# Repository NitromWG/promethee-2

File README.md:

# Prométhée

Logiciel libre d'ingénierie intégrée : CAO mécanique, mise en plan, CAO électronique et électrique dans un seul modèle. Le cahier des charges complet décrit le produit visé ; ce dépôt en est l'implémentation, construite étape par étape.

Le principe fondateur, déjà démontré : **la carte électronique et son boîtier forment un seul modèle**. Les piliers suivent les trous de fixation, les découpes de paroi suivent les connecteurs, les perçages du couvercle suivent les LED et les boutons, la hauteur du boîtier suit le composant le plus haut, et les vérifications tournent à chaque modification.

## État

Phase 0 (cadrage), voir [ETAT.md](ETAT.md) et [FEUILLE_DE_ROUTE.md](FEUILLE_DE_ROUTE.md).

| Partie | Contenu |
| --- | --- |
| `noyau/` | Modèle unique carte + boîtier, grandeurs dérivées, vérifications et corrections ; conception électronique (schéma, connectivité, ERC, circuit imprimé, zones, DRC, routage, fabrication, publication) (C++20) |
| `geometrie/` | Pièces exactes en B-rep OpenCascade, export STEP (noms, couleurs) et STL |
| `app/` | Application de bureau Qt 6 : vue Carte, vue Boîtier 3D OpenCascade, panneau, vérifications, nomenclature |
| `outils/` | `promethee`, l'outil en ligne de commande (mode sans écran) |
| `en-ligne/` | `promethee-en-ligne`, le seul programme qui ouvre le réseau (PLM, distributeurs, ERP, tickets), fonction par fonction et seulement si l'utilisateur l'active ; il lit et remplit les fichiers du dossier d'équipe, Prométhée ne voit que ces fichiers |
| `tests/` | Tests unitaires, géométriques, et comparaison cas par cas avec le prototype |
| `prototype-web/` | Prototype du jalon 0, implémentation de référence en JavaScript |
| `docs/adr/` | Décisions d'architecture |

## Essayer l'application sous Windows

Ouvrir l'onglet Actions du dépôt, cliquer sur la dernière compilation au vert, télécharger le paquet `Promethee-Windows`, le décompresser et lancer `Promethee.exe`. Aucune installation n'est nécessaire. Le paquet contient son LISEZMOI (lancement, journal, récupération, limites connues), la source correspondante, les licences, un inventaire SPDX et la somme SHA-256 de chaque fichier.

Apparence : Affichage › Thème, ou le choix « Apparence » de l'accueil. Prométhée (recommandé, par défaut) garde une interface bleu nuit autour de documents sur papier clair ; Clair, Sombre et Contraste élevé suivent ; Selon le système reprend le réglage clair ou sombre de Windows. Le changement est immédiat et gardé d'une session à l'autre ; l'impression et les PDF restent clairs.

Vue Carte : glisser un composant, un trou, ou une poignée du bord de la carte après avoir cliqué dessus ; molette pour zoomer ; double-clic pour pivoter un composant. Vue Boîtier : bouton gauche pour tourner autour, bouton droit pour déplacer, molette pour zoomer, cube de vue pour les vues normalisées (touches 0, 1, 3 et 7), boîtier transparent (T). La vue Carte montre la face avant ou la face arrière (B). Le boîtier se montre visible, transparent ou masqué ; le clic droit dans la 3D masque, rend transparent ou supprime un élément. Fichier propose l'import et l'export KiCad (.kicad_pcb), en mettant à jour la carte d'origine.

L'atelier électronique (Ctrl+3) conçoit une carte de bout en bout, sans autre logiciel : schéma (bibliothèque avec aperçu, fils en équerre, étiquettes, alimentations, annotation, vérification électrique en direct, dessin PDF), composants créés à partir de leur liste de broches, valeurs comprises (« 4k7 » = 4,7 kΩ) ou calculées (« 2*R1 »), circuit imprimé tenu à jour à chaque modification du schéma, les écarts risqués attendant au panneau des écarts (F8 synchronise tout), empreinte changée remplacée en place, composant remplacé par un autre article sans perdre ses fils, schéma et circuit côte à côte, placement à la souris, routage à 45° avec vérification d'isolement en direct (X piste, V via, / angle) ou automatique pour les liaisons simples, zones de cuivre, DRC, vue 3D, puis l'onglet Fabrication : santé de la conception, dossier Gerber X2 et Excellon, placement, nomenclature, publication R001… qui verrouille la révision. Ce qui ne se fabrique pas juste ne se publie pas, dérogation ou non : cuivre coupé par le bord, CMS sur la face sans cuivre d'une simple face, profil de fabricant inconnu, brochage non vérifié après un changement de boîtier. Un exemple complet (clignotant à NE555) s'ouvre depuis l'accueil. Schéma : W fil, L étiquette (Maj+L globale), P alimentation, Q non connecté, J jonction, T texte, A bibliothèque, R et Maj+R tourner, X et Y miroir, Origine tout voir ; circuit : F change de face. F1 donne la liste des raccourcis de l'atelier et de l'outil en cours. La souris suffit : chaque touche a son bouton au ruban (groupe Vue : Tout voir, zoom, inspecteur, raccourcis) ou au bandeau de l'outil (pendant une piste : Via, Dessus, Dessous, Retirer le coude, Retirer le tracé, Coude, Terminer), et un essai fait échouer la construction si une action n'a qu'un raccourci. Pendant un fil ou une piste, une autre commande (une jonction, une via à part, une piste gênante supprimée par le clic droit) suspend le tracé, qui reprend ensuite au dernier coude ; la barre du routeur choisit la paire de couches, la largeur, et le type et l'arrivée de la prochaine via. Le bandeau de sélection donne à la souris les modes Remplacer, Ajouter, Basculer et Retirer (Maj, Ctrl et Ctrl+Maj au clavier) ; un appui long immobile sur des objets superposés en ouvre la liste, comme Alt+clic ; le filtre de sélection de la barre d'état exclut des genres d'objets, et clignote quand il bloque un clic. Fichier › Réglages… (Ctrl+,) règle la souris et le pavé tactile : zoom par cran, sens de la molette, zoom autour du curseur ou du centre, défilement au bord pendant un glisser, deux doigts qui zooment ou font défiler, bouton des gestes. Menu à marques dans le schéma et le circuit : le bouton droit tenu immobile montre huit commandes (← Annuler, → Rétablir, ↑ Zoom sur la sélection, ↓ Tout voir, et en diagonale Tourner, Miroir, Supprimer, Dupliquer) ; avec Ctrl, un tracé rapide dans une direction lance la commande sans attendre. Le ruban est décrit par un fichier qui ne cite que des actions du registre (app/ressources/ruban_electronique.json) ; Réglages › Ruban le modifie en glissant une action dans un groupe, et « Rétablir l'original » le rend. Réglages › Clavier choisit si une touche d'outil l'arme ou agit au curseur. Les suites de deux touches existent (P puis V : poser une via au circuit), la première s'annonçant près du curseur ; Maj+A ouvre au curseur le menu Poser ; une bascule faite au clavier (/ : coude) s'annonce près du curseur. Dans l'atelier, les menus de la fenêtre sont les siens : Ctrl+I importe une carte KiCad vers l'électronique, Ctrl+E écrit le dossier de fabrication de la carte. « Schéma électronique » ouvre un schéma seul, dont le circuit imprimé se crée au premier besoin (bouton Circuit du ruban). Ctrl+3 dans un projet sans carte ouvre l'accueil électronique sans rien créer ; une carte se renomme sur place dans l'arbre, se supprime sans fenêtre (Ctrl+Z la rend), et un projet se rouvre sur le dernier atelier utilisé. Les panneaux de l'atelier (Projet, Bibliothèque, Inspecteur, Messages) flottent, s'ancrent, se groupent en onglets ou se ferment ; le bouton Panneaux de la barre d'état (ou Affichage › Panneaux et dispositions) enregistre leur disposition sous un nom, pour soi, dans le projet ou dans un fichier .json à partager, la rappelle et rend la disposition d'origine. La bibliothèque se trie par catégorie, par pertinence (accents ignorés) ou par ordre alphabétique, montre en colonnes les champs choisis d'un clic droit sur son en-tête, et son aperçu passe du symbole à l'empreinte, à la 3D et à la photo (propriété « photo » du composant). Fichier › Enregistrer pour une version précédente… écrit, pour un collègue qui n'a pas migré, un fichier neuf lisible par une version précédente, de la 0.33 à la 0.28 (« carte.pour-0-33.prom »), après la liste de ce qui s'y perd ; chaque migration du format a son inverse, et les schémas JSON de chaque version sont dans docs (schema_projet.json, schema_conception.json, docs/schemas). En ligne de commande : promethee pour-version <projet> <sortie> [version]. Le schéma se fait à la souris : un article se glisse de la bibliothèque sur la feuille (ou sur le circuit pour un trou de fixation), le survol montre l'objet visé et son infobulle, chaque objet a son menu au clic droit, le repère et la valeur s'éditent sur place, le fil part à l'équerre en évitant les symboles et les fils suivent un symbole déplacé ; la vérification électrique ne crie pas pendant le dessin et F7 la fait complète, son panneau groupant les problèmes par cause. Ctrl+F cherche dans tout le projet, schéma et circuit ; « Choisir les semblables » prend les composants de même valeur sur toutes les feuilles et estompe le reste ; une longueur et un angle se tapent pendant un fil (un chiffre ouvre la saisie). Les réglages se cherchent, s'exportent dans un fichier et se relisent, raccourcis, ruban et thème compris ; les couleurs du canevas se règlent une à une, avec une palette vérifiée pour les daltoniens. La fenêtre « Outils de conception » (ruban, groupe Outils) rassemble variantes et coût, revue automatique, comparaison avec un autre fichier, schéma de système, notes, historique local, mise en service et fiabilité, intégrité, logique, fabrication à l'atelier et exigences ; un projet tenu par un autre poste s'ouvre en consultation, avec le nom de celui qui le tient.

L'atelier électrique (Ctrl+4) mène un projet d'électricien de bout en bout, sans autre logiciel. Schéma sur folios CEI 61082 (139 symboles CEI 60617 avec leur fiche « C'est quoi ? », contacts rattachés à leur bobine, renvois croisés, bornes, numéros de fils, circuits types, vérification qui mène au problème d'un clic, appareils personnels dessinés d'après leurs bornes), armoire implantée à l'échelle avec son bilan thermique, faisceau, Grafcet (NF EN CEI 60848 : édition, vérification, simulation, folio, texte structuré pour l'automate), installation basse tension calculée (UTE C 15-105, note de calcul), photovoltaïque (UTE C 15-712-1), tableau de logement (NF C 15-100), boîte à calculs, rapports (nomenclature chiffrée, borniers, câbles, carnet de câblage, liste de coupe, chiffrage) et dossier complet (folios en PDF et en DXF, CSV, plans de perçage). Le bouton « Apprendre » ouvre des parcours guidés dont chaque étape se valide sur le projet. Un exemple (démarrage d'un moteur) s'ouvre depuis l'accueil, et les projets QElectroTech s'importent.

L'atelier Pièces (Ctrl+2) sert à concevoir une pièce de zéro : esquisses cotées et contraintes, extrusion, enlèvement, révolution, congé, chanfrein et coque, dans un arbre de construction modifiable à tout moment. Dans l'esquisseur : L ligne, R rectangle, C cercle, A arc, Maj+A arc par trois points, O rainure, Maj+P polygone, K ligne de construction, J congé, D cote (on clique les éléments, on place la cote, on tape la valeur), H et V. L'inventaire des fonctions prévues et faites est dans docs/FONCTIONNALITES.md. Le panneau règle la vis et l'insert de chaque trou, l'ancrage et le verrou de chaque composant. Le dossier de fabrication s'exporte en STEP, IGES, BREP, STL, 3MF, OBJ, PLY, DXF, SVG, CSV et projet. Fichier, Importer une carte KiCad (Ctrl+I) reprend une vraie carte (.kicad_pcb) avec son contour, ses trous et ses composants, et le boîtier épouse sa forme ; en ligne de commande : `promethee importer-kicad carte.kicad_pcb projet.prom.json`.

## Compiler sous Linux (Ubuntu 24.04)

```sh
sudo apt install cmake ninja-build g++ libtbb-dev catch2 nlohmann-json3-dev libfontconfig-dev libx11-dev \
  qt6-base-dev libgl-dev libglu1-mesa-dev \
  libocct-modeling-algorithms-dev libocct-modeling-data-dev libocct-data-exchange-dev \
  libocct-foundation-dev libocct-visualization-dev
cmake -S . -B build -G Ninja
cmake --build build
ctest --test-dir build --output-on-failure
build/app/Promethee
```

Sans Qt 6, tout le reste se compile et l'application de bureau est simplement ignorée. La CI construit aussi Windows (MSVC, vcpkg) et macOS (Homebrew).

## Utiliser l'outil

```sh
promethee exemple station.prom.json          # écrit le projet d'exemple
promethee verifier station.prom.json         # vérifie la carte et le boîtier
promethee corriger station.prom.json         # applique les corrections automatiques
promethee exporter station.prom.json sortie  # boitier.step, boitier.stl, couvercle.stl
promethee fabrication projet.prom sortie     # dossier de fabrication de la carte (Gerber, perçages, placement, nomenclature), contrôlé
promethee fabrication-exemple sortie         # la même chose pour la carte d'exemple
python3 tests/verifier_fabrication.py sortie # relecture indépendante du dossier (format, unités, origine, couches, trous)
promethee erc projet.prom --json             # ERC (aussi drc, revue, valider, exigences) ; code de sortie 1 s'il reste des erreurs
promethee sorties projet.prom jlcpcb         # un jeu de sorties, contrôlé avant d'écrire
promethee comparer a.prom b.prom             # différences par catégorie ; fusionner <ancêtre> <nous> <eux> <sortie>
promethee api projet.prom sortie.prom < requetes.jsonl  # requêtes JSON-RPC 2.0, une par ligne
```

L'application ouverte écoute aussi les mêmes requêtes JSON-RPC sur un canal local réservé à l'utilisateur (`promethee-<utilisateur>`, tube nommé sous Windows, socket Unix ailleurs), jamais sur un port réseau : chaque requête, ou chaque lot de requêtes, est un seul pas d'annulation. `promethee aide` liste toutes les commandes. Vérifier un projet à chaque envoi sur GitHub : [docs/integration-continue.md](docs/integration-continue.md).

Les fichiers `.prom.json` sont communs au prototype web et au logiciel natif.

## Licence et contributions

GPL-3.0 seule (voir [LICENSE](LICENSE)), sans double licence. Composants tiers et leurs licences : [TIERS.md](TIERS.md). Les contributions sont acceptées sous certificat d'origine du développeur (DCO) : chaque commit porte une ligne `Signed-off-by`. Détails dans [CONTRIBUER.md](CONTRIBUER.md).

## Essais de l'interface

« Promethee --essais-interface » rejoue un parcours complet en cliquant réellement dans la vue 3D et dans l'esquisseur (plans, esquisse, régions, esquisse sur face, coque, congé) et rend le nombre d'échecs. « Promethee --essais-onglets » rejoue les scénarios de documents et d'onglets, « Promethee --essais-electronique » le parcours de l'atelier électronique (schéma, circuit, routage, zone, DRC, composant créé, publication, révision), par de vrais gestes de souris et de clavier, sans signal émis ni action déclenchée à la main ; avec --onglets, le même parcours tourne dans la fenêtre à onglets, et l'intégration continue le lance aussi en 1 024 × 768. L'intégration continue les lance sous Linux à chaque envoi, et sous Windows sur le paquet tel qu'il est livré (rendu OpenGL logiciel). Le dossier de fabrication d'un corpus de sept cartes (`tests/audit_electronique/corpus_fabrication.cpp`) est relu à chaque envoi par des lecteurs écrits sans le code C++ : `tests/verifier_fabrication.py` (Gerber, Excellon, placement, nomenclature, IPC-D-356 et gbrjob champ par champ), gerbv et, s'il est installé, gerbonara. PROMETHEE_THEME=promethee|clair|sombre|contraste|systeme impose un thème sans le garder (captures, essais). Les mesures de performance se lancent à la demande : `build/tests/promethee_tests "[mesures]"`. Les cartes de mesure de l'atelier électronique s'écrivent par `promethee carte-mesure 300 carte.prom` (1 000, 2 000…) ; `build/tests/mesures_electronique` relève sur celles de 300, 1 000 et 2 000 composants le temps de chaque moteur (connectivité, ERC, plan de masse, DRC, synchronisation, lecture et écriture), et le parcours de l'atelier ajoute ceux des gestes sur la carte de 300 composants (lignes « MESURE ») ; l'intégration continue les écrit dans le résumé de chaque construction. « Promethee --electronique-demo schema|circuit|3d|fabrication|bibliotheque|composant » ouvre l'exemple électronique (avec --capture image.png pour une capture).

## Esquisse : raccourcis

Espace ouvre la ligne de commande (« c 50 » trace un cercle de Ø 50 coté, « r 40 30 » un rectangle, « ? » donne la liste) ; le clic droit maintenu ouvre le menu radial (haut : cote, bas : ligne, gauche : rectangle, droite : cercle) ; X bascule le mode construction ; Ctrl+Z et Ctrl+Y annulent et rétablissent dans l'esquisse ; Ctrl+Entrée ou la coche verte la terminent.

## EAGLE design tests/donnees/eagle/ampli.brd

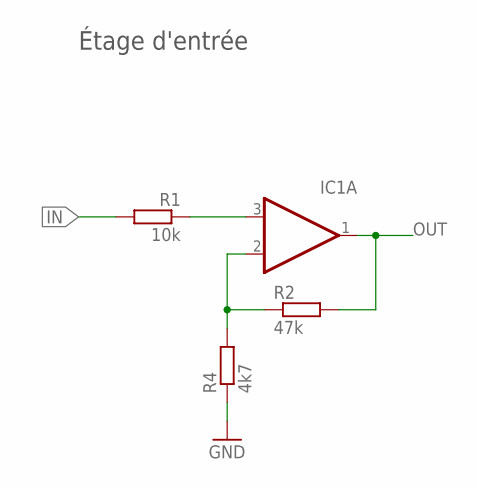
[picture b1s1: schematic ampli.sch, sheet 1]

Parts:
IC1: LM358N; DIL08
R1: 10k; R0603
R2: 47k; R0603
R4: 4k7; R0603

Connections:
GND: R4.1; also elsewhere on the board
IN: R1.2
unnamed: IC1.3 (+IN), R1.1
unnamed: IC1.2 (-IN), R2.1, R4.2
OUT: IC1.1 (OUT), R2.2; also elsewhere on the board

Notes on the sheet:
Étage d'entrée

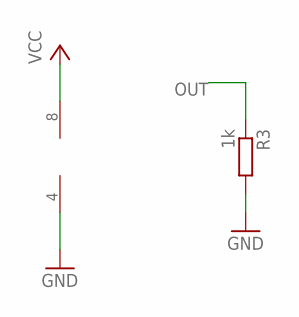
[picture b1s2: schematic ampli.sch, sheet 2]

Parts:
IC1: LM358N; DIL08
R3: 1k; R0603; MPN RC0603FR-071KL

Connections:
GND: IC1.4 (V-), R3.2; also elsewhere on the board
OUT: R3.1; also elsewhere on the board
VCC: IC1.8 (V+)

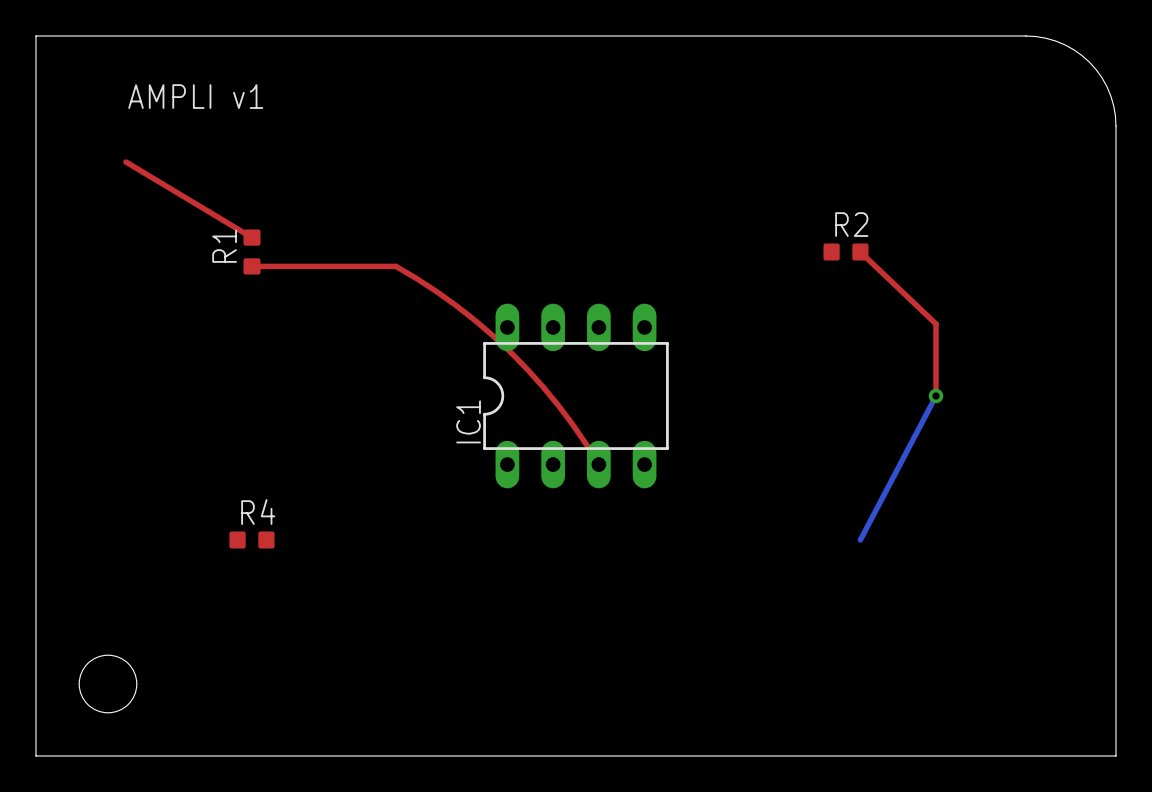
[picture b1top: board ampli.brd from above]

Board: 2 copper layers, 60.0 x 40.0 mm, 5 parts (1 on the bottom side), 4 nets.
